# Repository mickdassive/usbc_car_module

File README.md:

# USB 3.1x1 Hub with USB-C and USB-A Ports

This project is a USB 3.1x1 hub designed with KiCad 8.0 and developed with PlatformIO. It features two USB-C ports (one downstream and one upstream) capable of delivering up to 100W power, along with four regular downstream USB-A ports.

## Features

- USB 3.1x1 hub with USB-C and USB-A ports
- Supports up to 100W power delivery per port
- Onboard UART transceiver for programming the main MCU (ESP-12F)
- Onboard CAN bus transceiver for automotive applications
- Utilizes USB5926C hub chip from Microchip
- USB PD PHYs (PTN110N) from NXP
- Includes a display and ADC for power monitoring:
  - Monitor individual power consumption of USB-C ports (upstream and downstream)
  - Monitor combined total power consumption of USB-A ports
  - Monitor total system power consumption

## Contributors

- [Tokyo Andreana](https://github.com/mickdassive)

## License

This project is licensed under the [GNU General Public License v3.0](LICENSE).

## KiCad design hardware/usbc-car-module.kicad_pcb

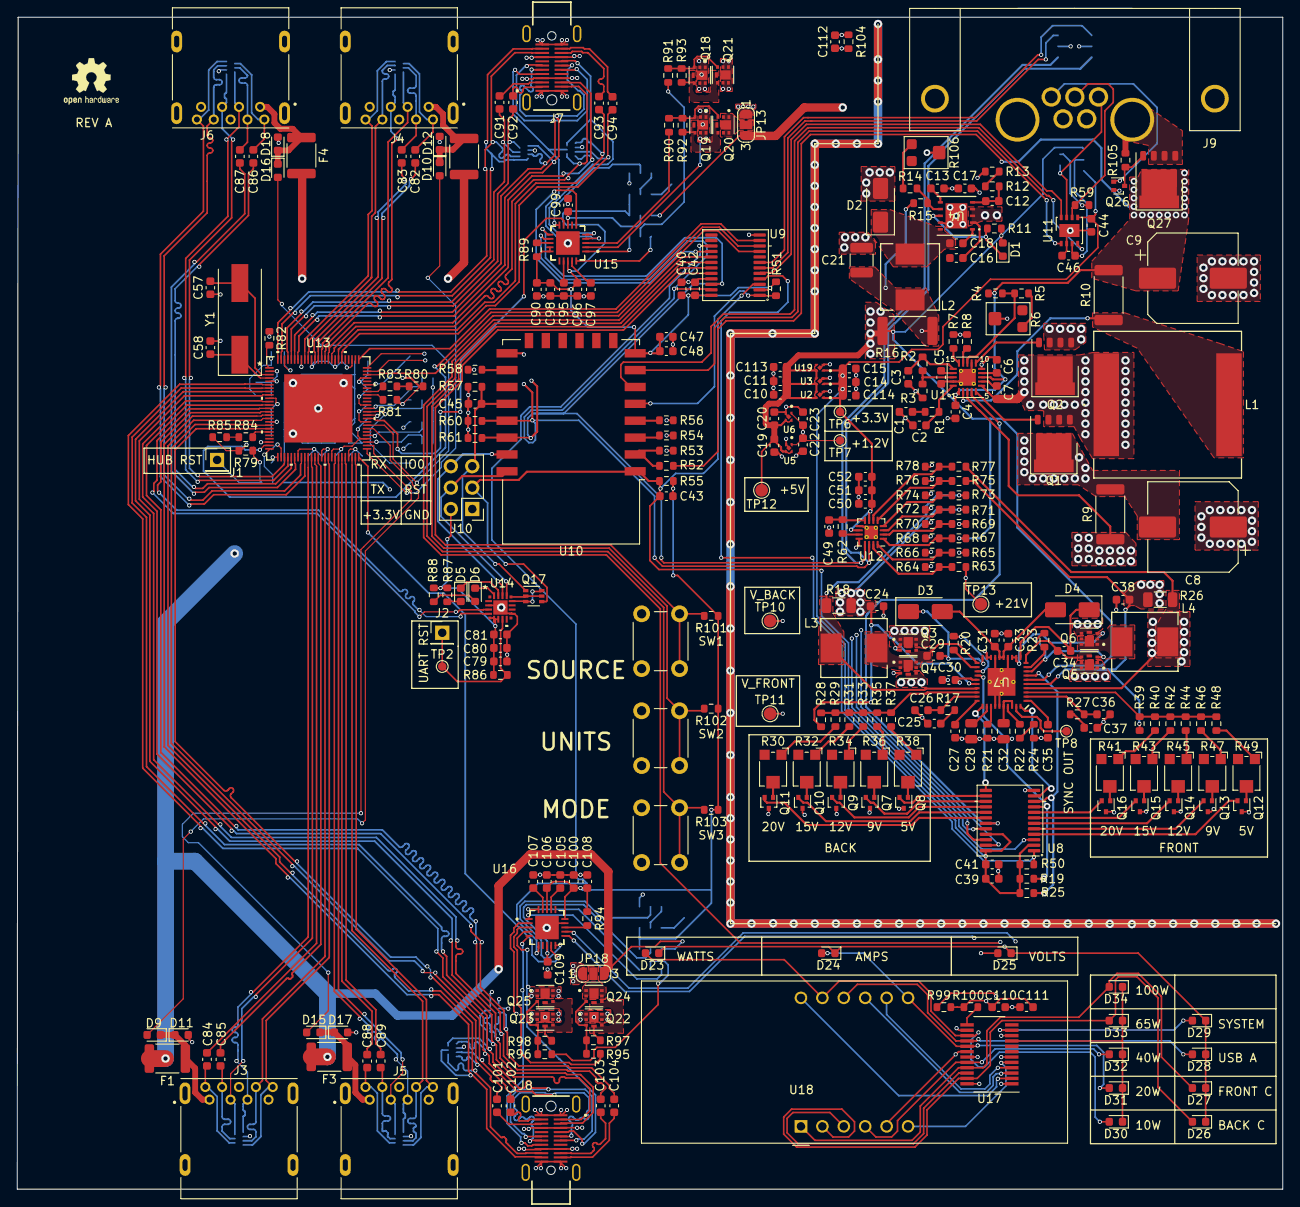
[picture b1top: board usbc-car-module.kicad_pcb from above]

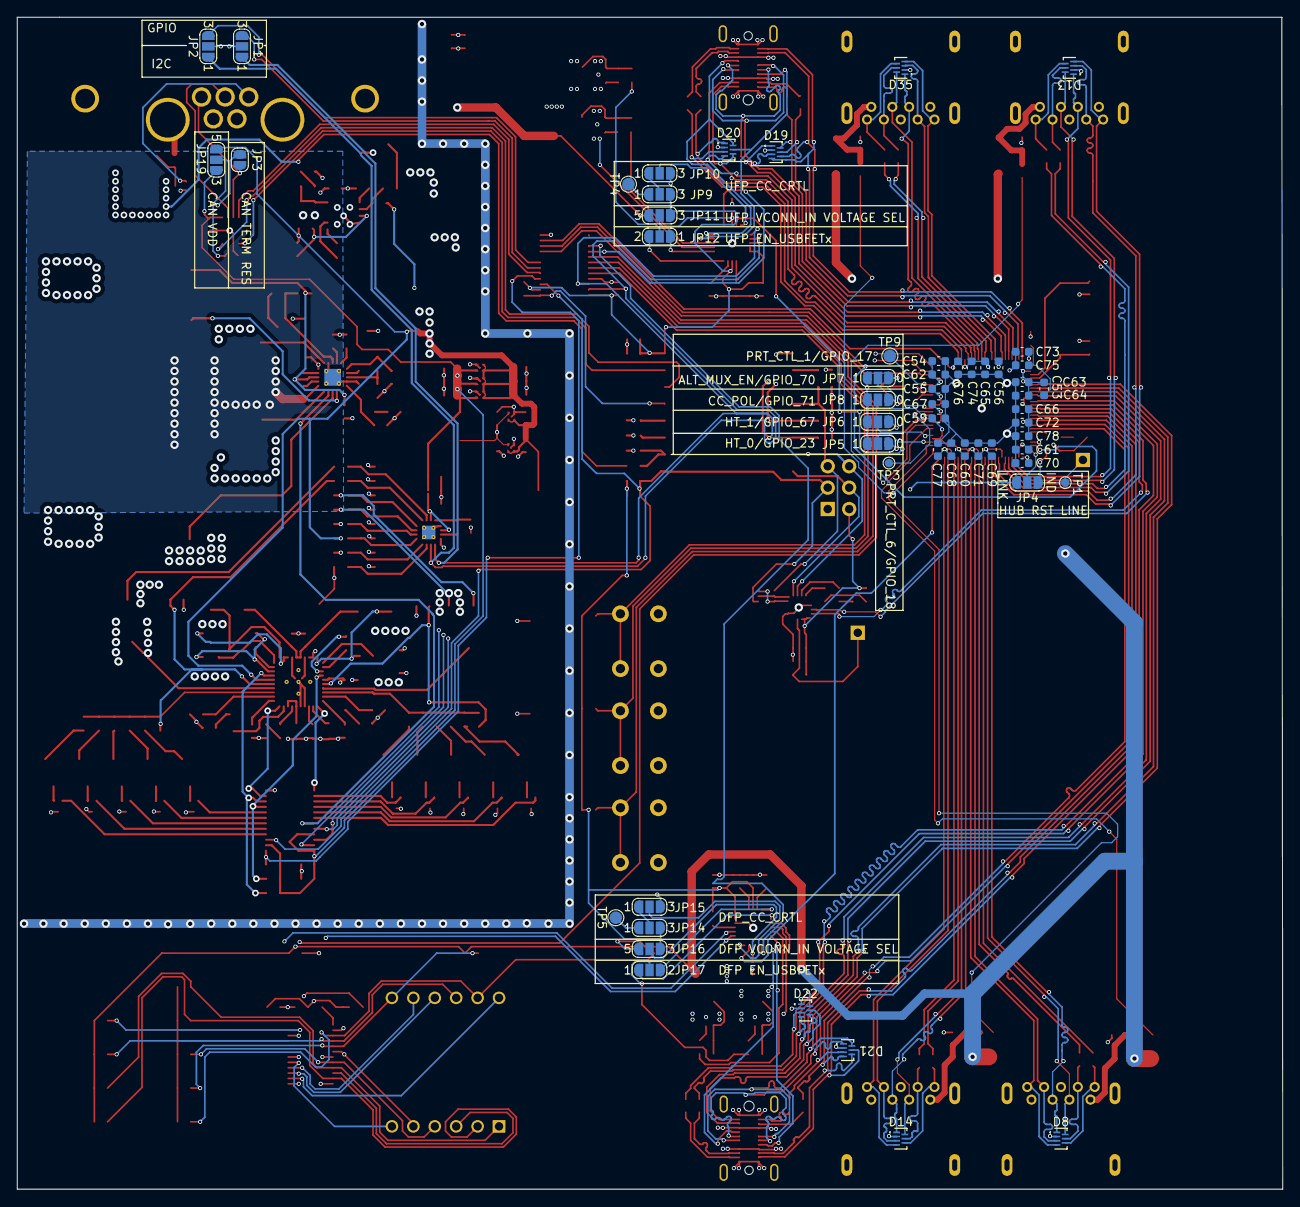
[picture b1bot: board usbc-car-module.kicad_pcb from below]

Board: 4 copper layers, 150.1 x 139.0 mm, 354 parts (54 on the bottom side), 290 nets.

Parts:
C1: 3uF3; C_0603_1608Metric
C2, C5, C7, C16, C18, C29, C34, C41, C42, C43, C44, C45, C46, C47, C50, C51, C55, C56, C59, C60, C61, C62, C63, C64, C65, C66, C67, C68, C69, C70, C71, C72, C73, C74, C76, C80, C81, C82, C83, C84, C85, C86, C87, C88, C89, C91, C92, C93, C94, C96, C98, C99, C101, C102, C103, C104, C106, C108, C109, C111, C112: 0.1uF; C_0603_1608Metric
C3, C4: 470pF; C_0603_1608Metric
C6, C17, C24, C25, C37, C38: 4.7uF; C_0603_1608Metric
C8: ouput cap EEEFK1V471SP 470uf; CP_Elec_10x10.5
C9: 120uF; CP_Elec_10x10.5
C10, C11, C13, C14, C15, C19, C20, C22, C23, C27, C35, C49, C113, C114: 1uF; C_0603_1608Metric
C12: 10pF; C_0603_1608Metric
C21: 15uF CGA6P3X7R1C156M250AB; C_1210_3225Metric
C26, C36, C57: 18pF; C_0603_1608Metric
C28, C32: 470nF; C_0805_2012Metric
C30: 50uF; C_0603_1608Metric
C31, C33, C95, C97, C105, C107: 2.2uF; C_0603_1608Metric
C39, C40, C48, C52, C53, C54, C75, C77, C78, C79, C90, C100, C110: 10uF; C_0603_1608Metric
C58: 18Pf; C_0603_1608Metric
D1, D5, D6: LED; D_0603_1608Metric
D2: SK510A-LTP; D_SMA
D3, D4: D_Shockley; D_SMA
D8, D13, D14, D19, D20, D21, D22, D35: PUSB3AB6Z_NEX
D9, D10, D15, D16: D; D_0603_1608Metric
D11, D12, D17, D18: uClamp0501H; D_0603_1608Metric
D23: W; D_0603_1608Metric
D24: A; D_0603_1608Metric
D25: V; D_0603_1608Metric
D26: BACK USBC POWER; D_0603_1608Metric
D27: FRONT USBC POWER; D_0603_1608Metric
D28: USBA POWER; D_0603_1608Metric
D29: TOTAL SYSTEM POWER; D_0603_1608Metric
D30: 10W; D_0603_1608Metric
D31: 20W; D_0603_1608Metric
D32: 40W; D_0603_1608Metric
D33: 65W; D_0603_1608Metric
D34: 100W; D_0603_1608Metric
F1, F3: 2A; Fuse_1812_4532Metric
F2, F4: 1A; Fuse_1812_4532Metric
J1, J2: PinHeader_1x01_P2.54mm_Vertical
J3, J4, J5, J6: 0483930003; MOLEX_0483930003
J7, J8: USB4200-03-A (VIRT FLAG MOUNTING); USB4200-03-A_REVA
J9: 684M7W2103L461
J10: PROG_PORT; PinHeader_2x03_P2.54mm_Vertical
JP1, JP2, JP4, JP5, JP6, JP7, JP8, JP9, JP10, JP11, JP12, JP13, JP14, JP15, JP16, JP17, JP18, JP19: SolderJumper-3_P1.3mm_Open_RoundedPad1.0x1.5mm_NumberLabels
JP3: SolderJumper-2_P1.3mm_Open_RoundedPad1.0x1.5mm
L1: IHLP6767GZER1R0M01; IND-6767GZ_VIS
L2: 1.2uH CR75NP-1R2MC; IND25X25CZ
L3, L4: IHLP2525CZER2R2M01; IND25X25CZ
Q1, Q2: NMOS; PQFN-8-EP_6x5mm_P1.27mm_Generic
Q3, Q4, Q5, Q6: PMPB11EN,115; TRANS_PMPB11EN_115
Q7, Q8, Q9, Q10, Q11, Q12, Q13, Q14, Q15, Q16, Q26: NMOS; SOT-416
Q17: BC847BS-7-F; SOT-363_SC-70-6
Q18, Q19, Q20, Q21, Q22, Q23, Q24, Q25: PMOS; TRANS_PMPB11EN_115
Q27: AON7421; PQFN-8-EP_6x5mm_P1.27mm_Generic
R1: 35K; R_0603_1608Metric
R2: 20K; R_0603_1608Metric
R3, R5, R7, R11, R12, R14, R22, R28, R33, R35, R39, R44, R46, R50, R51, R54, R55, R56, R57, R58, R63, R65, R67, R69, R71, R73, R75, R77, R79, R86, R89, R92, R93, R94, R97, R98, R99, R100, R101, R102, R103: 10K; R_0603_1608Metric
R4, R19, R25, R80, R83, R84, R85, R105: 100K; R_0603_1608Metric
R6, R106: 1K; Potentiometer_Bourns_TC33X_Vertical
R8, R21, R62: 0R; R_0603_1608Metric
R9, R10, R16: 1.5mR; R_2512_6332Metric
R13, R64, R66, R72, R74, R76, R78: 1K; R_0603_1608Metric
R15: 56K; R_0603_1608Metric
R17, R27: 5.9K; R_0603_1608Metric
R18, R26: 10mR; R_1206_3216Metric
R20: RHO1; R_0603_1608Metric
R23: RHO2; R_0603_1608Metric
R24, R53: 470R; R_0603_1608Metric
R29, R40: 30K; R_0603_1608Metric
R30, R32, R34, R36, R38, R41, R43, R45, R47, R49: 10K; Potentiometer_Bourns_TC33X_Vertical
R31, R42: 22K; R_0603_1608Metric
R37, R48, R68, R70: 5K; R_0603_1608Metric
R52, R60, R61: 10k; R_0603_1608Metric
R59: 120R; R_0603_1608Metric
R81: 10R; R_0603_1608Metric
R82: 12K 1%; R_0603_1608Metric
R87, R88, R104: 330R; R_0603_1608Metric
R90, R91, R95, R96: 15R; R_0603_1608Metric
SW1, SW2, SW3: SW_Push; SW_PUSH_6mm
TP1, TP3, TP6, TP7, TP8: TestPoint; TestPoint_Pad_D1.0mm
TP2: TestPoint_Pad_D1.0mm
TP4, TP5, TP9, TP10, TP11, TP12, TP13: TestPoint; TestPoint_Pad_D1.5mm
U1: LM51231-Q1; QFN-20-1EP_3.5x3.5mm_P0.5mm_EP2x2mm_ThermalVias
U2, U3, U19: NCP177BMX330TCG; VREG_NCP170AMX300TCG
U4: LMR14050-Q1; LMR14050
U5, U6: NCP177AMX120TCG; VREG_NCP170AMX300TCG
U7: LM5143
U8, U9: PI4IOE5V6416LEX; TSSOP-24_4.4x7.8mm_P0.65mm
U10: ESP-12F; ESP-12E
U11: MCP2558FD-xMF; DFN-8-1EP_3x3mm_P0.65mm_EP1.55x2.4mm
U12: WQFN-16-1EP_3x3mm_P0.5mm_EP1.6x1.6mm_ThermalVias
U13: VQFN100_KD_MCH
U14: CP2102N-QFN20; QFN20_SIL
U15, U16: PTN5100BSMP
U17: AS1115-BSST; QSOP-24_3.9x8.7mm_P0.635mm
U18: LTC-5723HR; CA56-12CGKWA
Y1: 25MHz; Crystal_SMD_HC49-SD

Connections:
5V_ADC: R67.2, R68.1, U12.1 (AIN2/GPIO2)
5V_CSN: C21.1, L2.2, R15.2, R16.1, R69.1
5V_CSN_ADC: R69.2, R70.1, U12.2 (AIN3/GPIO3)
21V_ADC: R63.2, R64.1, U12.15 (AIN0/GPIO0)
21V_COMP: C2.1, R1.1, U1.20 (COMP)
21V_CSN: C8.2, Q1.5 (D), R9.1, R65.1
21V_CSN_ADC: R65.2, R66.1, U12.16 (AIN1/GPIO1)
21V_PGOOD: U1.4 (PGOOD), U8.19 (P1_6)
+1V2: C22.1, C23.1, C65.2, C66.1, C67.2, C68.1, C69.2, C70.1, C71.2, C72.1, C73.2, C74.1, C75.2, C76.1, C77.2, C78.1, TP7.1, U5.1 (OUT), U6.1 (OUT), U13.10 (VDD12), U13.17 (VDD12), U13.26 (VDD12), U13.32 (VDD12), U13.39 (VDD12), U13.47 (VDD12), U13.59 (VDD12), U13.78 (VDD12), U13.83 (VDD12), U13.90 (VDD12), U13.98 (VDD12)
+3V3: C14.1, C15.1, C39.1, C40.1, C41.1, C42.1, C43.1, C44.2, C45.1, C47.1, C48.1, C50.1, C51.1, C52.1, C53.1, C54.2, C55.1, C56.2, C59.1, C60.2, C61.1, C62.2, C63.1, C64.2, C79.1, C80.1, C81.1, C90.1, C96.1, C98.1, C100.1, C106.1, C108.1, C110.1, C111.1, C114.1, J10.2, JP5.1 (A), JP6.1 (A), JP7.1 (A), JP8.1 (A), JP9.3 (B), JP11.3 (B), JP14.3 (B), JP16.3 (B), JP19.1 (A), R19.1, R25.2, R50.1, R51.1, R54.1, R55.1, R57.1, R60.1, R61.1, R79.2, R85.2, R86.1, R87.2, R88.2, R89.2, R94.2, R99.1, R100.1, R101.1, R102.1, R103.1, TP6.1, U2.1 (OUT), U3.1 (OUT), U8.2 (VDD_I2C), U8.21 (ADDR), U8.24 (VDD), U9.2 (VDD_I2C), U9.24 (VDD), U10.8 (VCC), U11.5 (VIO), U12.7 (AVDD), U12.10 (DVDD), U13.2 (VDD33), U13.5 (VDD33), U13.27 (VDD33), U13.42 (VDD33), U13.54 (VDD33), U13.64 (VDD33), U13.72 (VDD33), U13.93 (VDD33), U14.6 (VDD), U14.7 (VREGIN), U14.8 (VBUS), U15.14 (SLV_ADDR), U15.15 (VDD), U15.18 (VIO), U16.15 (VDD), U16.18 (VIO), U17.19 (VDD), U19.1 (OUT)
+5V: C10.1, C11.1, C19.1, C20.1, C113.1, D1.2 (A), F1.2, F2.2, F3.2, F4.2, JP11.1 (A), JP13.3 (B), JP16.1 (A), JP18.3 (B), JP19.3 (B), R11.1, R16.2, R67.1, TP12.1, U2.3 (EN), U2.4 (IN), U3.3 (EN), U3.4 (IN), U5.3 (EN), U5.4 (IN), U6.3 (EN), U6.4 (IN), U7.6 (VCCX), U19.3 (EN), U19.4 (IN)
+21V: C16.1, C17.1, C30.2, Q3.1 (D), Q3.2 (D), Q3.5 (D), Q3.6 (D), Q3.7 (D), Q5.1 (D), Q5.2 (D), Q5.5 (D), Q5.6 (D), Q5.7 (D), R9.2, R63.1, TP13.1, U1.3 (VOUT/SENSE), U4.2 (VIN), U4.3 (VIN), U4.4 (EN), U7.25 (VIN)
/5V USB-A AND MCU POWER/5V_BOOT: C18.1, U4.1 (BOOT)
/5V USB-A AND MCU POWER/5V_FB: R14.2, R15.1, U4.7 (FB)
/5V USB-A AND MCU POWER/5V_RT: R12.2, R13.1
/5V USB-A AND MCU POWER/5V_SS: C13.1, U4.6 (SS)
/5V USB-A AND MCU POWER/5V_SW: C18.2, D2.1 (K), L2.1, U4.10 (SW)
/12-21V INPUT BOOST CONVERTER/21V_COMP_1: C1.1, R1.2
/12-21V INPUT BOOST CONVERTER/21V_VCC: C6.1, U1.9 (VCC)
/12-21V INPUT BOOST CONVERTER/CSN: L1.2, R10.1, U1.2 (CSN)
/12-21V INPUT BOOST CONVERTER/HB: C7.1, U1.7 (HB)
/12-21V INPUT BOOST CONVERTER/HI_SW: Q1.4 (G), U1.5 (HO)
/12-21V INPUT BOOST CONVERTER/LO_SW: Q2.4 (G), U1.11 (LO)
/12-21V INPUT BOOST CONVERTER/RT: R7.2, U1.15 (RT)
/12-21V INPUT BOOST CONVERTER/SS: C5.2, U1.17 (SS)
/12-21V INPUT BOOST CONVERTER/SW: C7.2, L1.1, Q1.1 (S), Q1.2 (S), Q1.3 (S), Q2.5 (D), U1.6 (SW)
/12-21V INPUT BOOST CONVERTER/TRK: R2.2, R3.1, U1.18 (TRK)
/12-21V INPUT BOOST CONVERTER/UVLO/EN: R4.2, R5.1, U1.13 (UVLO/EN)
/12-21V INPUT BOOST CONVERTER/VREF: C3.1, R2.1, U1.16 (VREF/RANGE)
/BACK_UFP_USB_C_PORT/UFP_TXA_N: C91.1, J7.A3 (TX1-)
/BACK_UFP_USB_C_PORT/UFP_TXA_P: C92.2, J7.A2 (TX1+)
/BACK_UFP_USB_C_PORT/UFP_TXB_N: C93.1, J7.B3 (TX2-)
/BACK_UFP_USB_C_PORT/UFP_TXB_P: C94.2, J7.B2 (TX2+)
/FRONT_DFP_USB_C_PORT/DFP_RXA_N: C103.1, J8.A10 (RX2-)
/FRONT_DFP_USB_C_PORT/DFP_RXA_P: C104.2, J8.A11 (RX2+)
/FRONT_DFP_USB_C_PORT/DFP_RXB_N: C101.1, J8.B10 (RX1-)
/FRONT_DFP_USB_C_PORT/DFP_RXB_P: C102.2, J8.B11 (RX1+)
/USBA_PORTS/P2_2_N: D8.7 (CH6), J3.2 (D-), U13.36 (USB2DN_DM3/PRT_DIS_M3)
/USBA_PORTS/P2_2_P: D8.1 (CH1), J3.3 (D+), U13.35 (USB2DN_DP3/PRT_DIS_P3)
/USBA_PORTS/P2_RX_N: D8.4 (CH3), J3.5 (STDA_SSRX-), U13.41 (USB3DN_RXDM3)
/USBA_PORTS/P2_RX_P: D8.3 (CH2), J3.6 (STDA_SSRX+), U13.40 (USB3DN_RXDP3)
/USBA_PORTS/P2_TXP_N: C85.1, D8.6 (CH5), J3.8 (STDA_SSTX-)
/USBA_PORTS/P2_TXP_P: C84.2, D8.5 (CH4), J3.9 (STDA_SSTX+)
/USBA_PORTS/P2_TX_N: C85.2, U13.38 (USB3DN_TXDM3)
/USBA_PORTS/P2_TX_P: C84.1, U13.37 (USB3DN_TXDP3)
/USBA_PORTS/P3_2_N: D14.7 (CH6), J5.2 (D-), U13.44 (USB2DN_DM4/PRT_DIS_M4)
/USBA_PORTS/P3_2_P: D14.1 (CH1), J5.3 (D+), U13.43 (USB2DN_DP4/PRT_DIS_P4)
/USBA_PORTS/P3_RX_N: D14.4 (CH3), J5.5 (STDA_SSRX-), U13.49 (USB3DN_RXDM4)
/USBA_PORTS/P3_RX_P: D14.3 (CH2), J5.6 (STDA_SSRX+), U13.48 (USB3DN_RXDP4)
/USBA_PORTS/P3_TXP_N: C89.1, D14.6 (CH5), J5.8 (STDA_SSTX-)
/USBA_PORTS/P3_TXP_P: C88.2, D14.5 (CH4), J5.9 (STDA_SSTX+)
/USBA_PORTS/P3_TX_N: C89.2, U13.46 (USB3DN_TXDM4)
/USBA_PORTS/P3_TX_P: C88.1, U13.45 (USB3DN_TXDP4)
/USBA_PORTS/P4_2_N: D35.7 (CH6), J4.2 (D-), U13.87 (USB2DN_DM5/PRT_DIS_M5)
/USBA_PORTS/P4_2_P: D35.1 (CH1), J4.3 (D+), U13.86 (USB2DN_D5/PRT_DIS_P5)
/USBA_PORTS/P4_RX_N: D35.4 (CH3), J4.5 (STDA_SSRX-), U13.92 (USB3DN_RXDM5)
/USBA_PORTS/P4_RX_P: D35.3 (CH2), J4.6 (STDA_SSRX+), U13.91 (USB3DN_RXDP5)
/USBA_PORTS/P4_TXP_N: C83.1, D35.6 (CH5), J4.8 (STDA_SSTX-)
/USBA_PORTS/P4_TXP_P: C82.2, D35.5 (CH4), J4.9 (STDA_SSTX+)
/USBA_PORTS/P4_TX_N: C83.2, U13.89 (USB3DN_TXDM5)
/USBA_PORTS/P4_TX_P: C82.1, U13.88 (USB3DN_TXDP5)
/USBA_PORTS/P5_2_N: D13.7 (CH6), J6.2 (D-), U13.29 (USB2DN_DM2/PRT_DIS_M2)
/USBA_PORTS/P5_2_P: D13.1 (CH1), J6.3 (D+), U13.28 (USB2DN_DP2/PRT_DIS_P2)
/USBA_PORTS/P5_RX_N: D13.4 (CH3), J6.5 (STDA_SSRX-), U13.34 (USB3DN_RXDM2)
/USBA_PORTS/P5_RX_P: D13.3 (CH2), J6.6 (STDA_SSRX+), U13.33 (USB3DN_RXDP2)
/USBA_PORTS/P5_TXP_N: C87.1, D13.6 (CH5), J6.8 (STDA_SSTX-)
/USBA_PORTS/P5_TXP_P: C86.2, D13.5 (CH4), J6.9 (STDA_SSTX+)
/USBA_PORTS/P5_TX_N: C87.2, U13.31 (USB3DN_TXDM2)
/USBA_PORTS/P5_TX_P: C86.1, U13.30 (USB3DN_TXDP2)
/USB_UART/USB_UART_N: U13.14 (USB2DN_DM6/PRT_DIS_M6), U14.5 (D-)
/USB_UART/USB_UART_P: U13.13 (USB2DN_DP6/PRT_DIS_P6), U14.4 (D+)
ADC_ALERT: U8.20 (P1_7), U12.12 (ALERT)
B_SUB-C_BUCK_P-GOOD: R19.2, U7.24 (PG1), U8.9 (P0_5)
B_USB-C_BUCK_5V_SEL: Q8.2 (G), U8.14 (P1_1)
B_USB-C_BUCK_9V_SEL: Q7.2 (G), U8.15 (P1_2)
B_USB-C_BUCK_12V_SEL: Q9.2 (G), U8.16 (P1_3)
B_USB-C_BUCK_15V_SEL: Q10.2 (G), U8.17 (P1_4)
B_USB-C_BUCK_20V_SEL: Q11.2 (G), U8.18 (P1_5)
B_USB-C_BUCK_EN: U7.31 (EN1), U8.13 (P1_0)
B_USB-C_BUCK_FB: R28.2, R29.1, R31.1, R33.1, R35.1, R37.1, U7.28 (FB1)
B_USB-C_BUCK_OUT: C24.1, JP13.1 (A), Q21.1 (D), Q21.2 (D), Q21.5 (D), Q21.6 (D), Q21.7 (D), R18.1, R28.1, R71.1, TP10.1, U7.26 (VOUT1)
B_USB-C_BUCK_OUT_ADC: R71.2, R72.1, U12.3 (AIN4/GPIO4)
B_USB-C_CSN: L3.1, R18.2, R73.1, U7.27 (CS1)
B_USB-C_CSN_ADC: R73.2, R74.1, U12.4 (AIN5/GPIO5)
CAN_H: J9.3, JP3.2 (B), U11.7 (CANH)
CAN_L: J9.4, R59.2, U11.6 (CANL)
CAN_RX: U10.6 (GPIO12), U11.4 (RXD)
CAN_SILENT: U9.5 (P0_1), U11.8 (S)
CAN_TX: U10.7 (GPIO13), U11.1 (TXD)
CAR_12V_IN: C4.1, C9.1, Q27.5 (D), R4.1, R10.2, R52.1, U1.1 (CSP), U1.8 (BIAS)
DFP_2_N: D21.7 (CH6), J8.A7 (D-), J8.B7 (D-), U13.7 (USB2DN_DM1/PRT_DIS_M1)
DFP_2_P: D21.1 (CH1), J8.A6 (D+), J8.B6 (D+), U13.6 (USB2DN_DP1/PRT_DIS_P1)
DFP_3_RXA_N: C103.2, D22.4 (CH3), U13.12 (USB3DN_RXDM1A)
DFP_3_RXA_P: C104.1, D22.3 (CH2), U13.11 (USB3DN_RXDP1A)
DFP_3_RXB_N: C101.2, D21.4 (CH3), U13.19 (USB3DN_RXDM1B)
DFP_3_RXB_P: C102.1, D21.3 (CH2), U13.18 (USB3DN_RXDP1B)
DFP_3_TXA_N: D22.5 (CH4), J8.A3 (TX1-), U13.9 (USB3DN_TXDM1A)
DFP_3_TXA_P: D22.6 (CH5), J8.A2 (TX1+), U13.8 (USB3DN_TXDP1A)
DFP_3_TXB_N: D21.5 (CH4), J8.B3 (TX2-), U13.16 (USB3DN_TXDM1B)
DFP_3_TXB_P: D21.6 (CH5), J8.B2 (TX2+), U13.15 (USB3DN_TXDP1B)
DFP_CC1: D22.7 (CH6), J8.A5 (CC1), U16.4 (CC2)
DFP_CC2: D22.1 (CH1), J8.B5 (CC2), U16.5 (CC1)
DFP_CC_CTRL: JP15.2 (C), U16.10 (CC_CRTL1)
DFP_CC_ORIENT: U13.50 (AB1/ATTACHMUX1B/GPIO65), U16.9 (CC_ORIENT)
DFP_C_ATTACH_1: U9.9 (P0_5), U13.73 (C_ATTACH1/ATTACHMUX1A/GPIO1)
DFP_DBGACC: U9.15 (P1_2), U16.6 (DBGACC_FOUND)
DFP_PD_INT: R94.1, U16.13 (INT_N)
DFP_VBUS: J8.A4 (VBUS), J8.A9 (VBUS), J8.B4 (VBUS), J8.B9 (VBUS), Q22.1 (D), Q22.2 (D), Q22.5 (D), Q22.6 (D), Q22.7 (D), Q23.1 (D), Q23.2 (D), Q23.5 (D), Q23.6 (D), Q23.7 (D), U16.2 (VBUS)
DISP_DIG_0: U17.2 (DIG0), U18.12 (CC1)
DISP_DIG_1: U17.3 (DIG1), U18.9 (CC2)
DISP_DIG_2: U17.4 (DIG2), U18.8 (CC3)
DISP_DIG_3: U17.5 (DIG3), U18.6 (CC4)
DISP_DIG_6: D30.1 (K), D31.1 (K), D32.1 (K), D33.1 (K), D34.1 (K), U17.9 (DIG6)
DISP_DIG_7: D23.1 (K), D24.1 (K), D25.1 (K), D26.1 (K), D27.1 (K), D28.1 (K), D29.1 (K), U17.10 (DIG7)
DISP_IRQ: R99.2, U9.17 (P1_4), U17.24 (IRQ)
DISP_SEG_A: D23.2 (A), D30.2 (A), U17.15 (SEGA), U18.11 (a)
DISP_SEG_B: D24.2 (A), D31.2 (A), U17.17 (SEGB), U18.7 (b)
DISP_SEG_C: D25.2 (A), D32.2 (A), U17.20 (SEGC), U18.4 (c)
DISP_SEG_D: D26.2 (A), D33.2 (A), U17.23 (SEGD), U18.2 (d)
DISP_SEG_DP: U17.22 (SEGDP), U18.3 (DPX)
DISP_SEG_E: D27.2 (A), D34.2 (A), U17.21 (SEGE), U18.1 (e)
DISP_SEG_F: D28.2 (A), U17.16 (SEGF), U18.10 (f)
DISP_SEG_G: D29.2 (A), U17.11 (KEYA), U17.18 (SEGG), U18.5 (g)
DSUB_P_6: J9.6, JP2.2 (C)
DSUB_P_7: J9.7, JP1.2 (C)
ESP_EN: R54.2, U10.3 (EN)
ESP_IO0: C45.2, J10.5, Q17.1 (C1), R57.2, U10.18 (GPIO0)
ESP_RX: J10.6, U10.21 (GPIO3/RXD), U14.18 (TXD)
ESP_TX: J10.4, U10.22 (GPIO1/TXD), U14.17 (RXD)
F_SUB-C_BUCK_P-GOOD: R25.1, U7.7 (PG2), U8.10 (P0_6)
F_USB-C_BUCK_5V_SEL: Q12.2 (G), U8.4 (P0_0)
F_USB-C_BUCK_9V_SEL: Q13.2 (G), U8.5 (P0_1)
F_USB-C_BUCK_12V_SEL: Q14.2 (G), U8.6 (P0_2)
F_USB-C_BUCK_15V_SEL: Q15.2 (G), U8.7 (P0_3)
F_USB-C_BUCK_20V_SEL: Q16.2 (G), U8.8 (P0_4)
F_USB-C_BUCK_EN: U7.40 (EN2), U8.11 (P0_7)
F_USB-C_BUCK_FB: R39.2, R40.1, R42.1, R44.1, R46.1, R48.1, U7.3 (FB2)
F_USB-C_BUCK_OUT: C38.1, JP18.1 (A), Q25.1 (D), Q25.2 (D), Q25.5 (D), Q25.6 (D), Q25.7 (D), R26.2, R39.1, R75.1, TP11.1, U7.5 (VOUT2)
F_USB-C_BUCK_OUT_ADC: R75.2, R76.1, U12.5 (AIN6/GPIO6)
F_USB-C_CSN: L4.2, R26.1, R77.1, U7.4 (CS2)
F_USB-C_CSN_ADC: R77.2, R78.1, U12.6 (AIN7/GPIO7)
GND: C1.2, C2.2, C3.2, C4.2, C5.1, C6.2, C8.1, C9.2, C10.2, C11.2, C13.2, C14.2, C15.2, C16.2, C17.2, C19.2, C20.2, C21.2, C22.2, C23.2, C24.2, C25.1, C26.1, C27.1, C28.1, C30.1, C31.2, C32.1, C33.2, C35.1, C36.2, C37.2, C38.2, C39.2, C40.2, C41.2, C42.2, C44.1, C46.2, C47.2, C48.2, C49.2, C50.2, C51.2, C52.2, C53.2, C54.1, C55.2, C56.1, C57.1, C58.1, C59.2, C60.1, C61.2, C62.1, C63.2, C64.1, C65.1, C66.2, C67.1, C68.2, C69.1, C70.2, C71.1, C72.2, C73.1, C74.2, C75.1, C76.2, C77.1, C78.2, C79.2, C80.2, C81.2, C90.2, C95.2, C96.2, C97.2, C98.2, C99.2, C100.2, C105.2, C106.2, C107.2, C108.2, C109.2, C110.2, C111.2, C112.1, C113.2, C114.2, D2.2 (A), D8.2 (GND), D11.2 (A), D12.2 (A), D13.2 (GND), D14.2 (GND), D17.2 (A), D18.2 (A), D19.2 (GND), D20.2 (GND), D21.2 (GND), D22.2 (GND), D35.2 (GND), J3.4 (GND), J3.7 (GND_DRAIN), J4.4 (GND), J4.7 (GND_DRAIN), J5.4 (GND), J5.7 (GND_DRAIN), J6.4 (GND), J6.7 (GND_DRAIN), J7.A1 (GND), J7.A12 (GND), J7.B1 (GND), J7.B12 (GND), J8.A1 (GND), J8.A12 (GND), J8.B1 (GND), J8.B12 (GND), J9.2, J10.1, JP5.3 (B), JP6.3 (B), JP7.3 (B), JP8.3 (B), JP10.3 (B), JP15.3 (B), Q2.1 (S), Q2.2 (S), Q2.3 (S), Q4.4 (S), Q4.8 (S), Q6.4 (S), Q6.8 (S), Q7.3 (S), Q8.3 (S), Q9.3 (S), Q10.3 (S), Q11.3 (S), Q12.3 (S), Q13.3 (S), Q14.3 (S), Q15.3 (S), Q16.3 (S), Q26.2 (S), R3.2, R6.2, R7.1, R8.2, R13.2, R21.2, R24.2, R53.2, R56.2, R58.2, R64.2, R66.2, R68.2, R70.2, R72.2, R74.2, R76.2, R78.2, R80.2, R81.2, R82.1, R104.1, R106.2, SW1.2, SW2.2, SW3.2, U1.10 (PGND), U1.12 (MODE), U1.19 (AGND), U1.21 (EP), U2.2 (GND), U2.5 (EP), U3.2 (GND), U3.5 (EP), U4.9 (GND), U4.11 (EP), U5.2 (GND), U5.5 (EP), U6.2 (GND), U6.5 (EP), U7.14 (PGND2), U7.17 (PGND1), U7.34 (MODE), U7.35 (AGND), U7.41 (EP), U8.12 (VSS), U9.12 (VSS), U9.21 (ADDR), U10.15 (GND), U11.2 (VSS), U11.9 (VSS), U12.9 (GND), U12.17 (EP), U13.23 (TESTEN), U13.101 (VSS/GND), U14.3 (GND), U14.12 (GND), U14.21 (GND), U15.21 (GND), U16.14 (SLV_ADDR), U16.21 (GND), U17.6 (GND), U19.2 (GND), U19.5 (EP)
GNDS: C112.2, J3.S, J4.S, J5.S, J6.S, J7.S (SHIELD), J8.S (SHIELD), J9.S, R104.2
HUB_VBUS_DET: U9.10 (P0_6), U13.24 (VBUS_DET)
I2C_SCL: JP1.1 (A), R61.2, U8.22 (SCL), U9.22 (SCL), U10.20 (GPIO5), U12.13 (SCL), U13.75 (SMBCLK/GPIO8/SCL), U15.11 (SPI_CLK_I2C_SCL), U16.11 (SPI_CLK_I2C_SCL), U17.14 (SCL)
I2C_SDA: JP2.1 (A), R60.2, U8.23 (SDA), U9.23 (SDA), U10.19 (GPIO4), U12.14 (SDA), U13.74 (SMBDATA/GPIO6/SDA), U15.12 (SPI_MOSI_I2C_SDA), U16.12 (SPI_MOSI_I2C_SDA), U17.1 (SDA)
IOX0_INT: R51.2, U9.1 (INT), U10.5 (GPIO14)
IOX1_INT: R50.2, U8.1 (INT), U9.4 (P0_0)
IOX_0_P_0_0: JP2.3 (B), U9.7 (P0_3)
IOX_0_P_0_1: JP1.3 (B), U9.6 (P0_2)
MAIN BOOST CLOCK IN: R8.1, U1.14 (SYNC/DITHER/EN)
MODE_BTN: R103.2, SW3.1, U9.18 (P1_5)
unnamed: C25.2, R17.1
unnamed: C37.1, R27.2
unnamed: D1.1 (K), R11.2, U4.8 (PGOOD)
unnamed: C31.1, C33.1, D3.2 (A), D4.2 (A), U7.15 (VCC), U7.16 (VCC)
unnamed: C29.2, D3.1 (K), U7.20 (HB1)
unnamed: C34.1, D4.1 (K), U7.11 (HB2)
unnamed: D5.2 (A), R87.1
unnamed: D5.1 (K), U14.19 (~RXT/GPIO.3)
unnamed: D6.2 (A), R88.1
unnamed: D6.1 (K), U14.20 (~TXT/GPIO.2)
unnamed: D9.2 (A), U13.57 (PRT_CTL3/GANG_PWR/GPIO20)
unnamed: D10.2 (A), U13.51 (PRT_CTL5/GPIO22)
unnamed: D10.1 (K), D12.1 (K), F2.1, J4.1 (VBUS)
unnamed: D9.1 (K), D11.1 (K), F1.1, J3.1 (VBUS)
unnamed: D15.2 (A), U13.52 (PRT_CTL4/GPIO21)
unnamed: D15.1 (K), D17.1 (K), F3.1, J5.1 (VBUS)
unnamed: D16.2 (A), U13.58 (PRT_CTL2/GPIO19)
unnamed: D16.1 (K), D18.1 (K), F4.1, J6.1 (VBUS)
unnamed: J1.1, JP4.1 (A), R79.1, TP1.1
unnamed: J9.1, Q27.1 (S), Q27.2 (S), Q27.3 (S), R105.1
unnamed: JP3.1 (A), R59.1
unnamed: JP4.2 (C), U13.25 (RESET_N)
unnamed: JP5.2 (C), U13.53 (HOST_TYPE0/GPIO23)
unnamed: JP6.2 (C), U13.55 (HOST_TYPE1/GPIO67)
unnamed: JP7.2 (C), U13.63 (ALT_MUX_EN/GPIO70)
unnamed: JP8.2 (C), U13.61 (CC_POL/GPIO71)
unnamed: JP9.1 (A), TP4.1
unnamed: JP9.2 (C), JP10.1 (A)
unnamed: C99.1, JP11.2 (C), U15.8 (VCONN_IN)
unnamed: JP12.1 (A), U15.20 (EN_USBFET2)
unnamed: JP12.3 (B), U15.1 (EN_USBFET1)
unnamed: JP12.2 (C), R91.1
unnamed: JP13.2 (C), Q20.1 (D), Q20.2 (D), Q20.5 (D), Q20.6 (D), Q20.7 (D)
unnamed: JP14.1 (A), TP5.1
unnamed: JP14.2 (C), JP15.1 (A)
unnamed: C109.1, JP16.2 (C), U16.8 (VCONN_IN)
unnamed: JP17.1 (A), U16.1 (EN_USBFET1)
unnamed: JP17.3 (B), U16.20 (EN_USBFET2)
unnamed: JP17.2 (C), R96.1
unnamed: JP18.2 (C), Q24.1 (D), Q24.2 (D), Q24.5 (D), Q24.6 (D), Q24.7 (D)
unnamed: C46.1, JP19.2 (C), U11.3 (VDD)
unnamed: Q3.3 (G), R20.1, U7.23 (HOL1)
unnamed: Q4.3 (G), U7.18 (LO1), U7.19 (LOL1)
unnamed: Q5.3 (G), R23.2, U7.8 (HOL2)
unnamed: Q6.3 (G), U7.12 (LOL2), U7.13 (LO2)
unnamed: Q7.1 (D), R36.2
unnamed: Q8.1 (D), R38.2
unnamed: Q9.1 (D), R34.2
unnamed: Q10.1 (D), R32.2
unnamed: Q11.1 (D), R30.2
unnamed: Q12.1 (D), R49.2
unnamed: Q13.1 (D), R47.2
unnamed: Q14.1 (D), R45.2
unnamed: Q15.1 (D), R43.2
unnamed: Q16.1 (D), R41.2
unnamed: Q17.2 (B1), Q17.5 (E2), U14.16 (~RTS)
unnamed: Q17.3 (B2), Q17.6 (E1), U14.15 (~CTS)
unnamed: Q18.3 (G), Q21.3 (G), R91.2, R93.2
unnamed: Q18.4 (S), Q18.8 (S), Q21.4 (S), Q21.8 (S), R93.1
unnamed: Q19.3 (G), Q20.3 (G), R90.2, R92.2
unnamed: Q19.4 (S), Q19.8 (S), Q20.4 (S), Q20.8 (S), R92.1
unnamed: Q22.3 (G), Q24.3 (G), R95.2, R97.2
unnamed: Q22.4 (S), Q22.8 (S), Q24.4 (S), Q24.8 (S), R97.1
unnamed: Q23.3 (G), Q25.3 (G), R96.2, R98.2
unnamed: Q23.4 (S), Q23.8 (S), Q25.4 (S), Q25.8 (S), R98.1
unnamed: Q26.3 (D), Q27.4 (G), R105.2
unnamed: J9.5, Q26.1 (G)
unnamed: R5.2, R6.1
unnamed: R22.2, R24.1
unnamed: R29.2, R30.1
unnamed: R31.2, R32.1
unnamed: R33.2, R34.1
unnamed: R35.2, R36.1
unnamed: R37.2, R38.1
unnamed: R40.2, R41.1
unnamed: R42.2, R43.1
unnamed: R44.2, R45.1
unnamed: R46.2, R47.1
unnamed: R48.2, R49.1
unnamed: R80.1, R83.2
unnamed: R84.2, R85.1
unnamed: R14.1, R106.1
unnamed: C26.2, R17.2, U7.29 (COMP1)
unnamed: C36.1, R27.1, U7.2 (COMP2)
unnamed: C32.2, U7.36 (VDDA), U7.38 (DITH)
unnamed: R20.2, U7.22 (HO1)
unnamed: R23.1, U7.9 (HO2)
unnamed: C28.2, U7.32 (RES)
unnamed: R22.1, U7.37 (RT)
unnamed: C27.2, U7.30 (SS1)
unnamed: C35.2, U7.1 (SS2)
unnamed: C29.1, L3.2, Q3.4 (S), Q3.8 (S), Q4.1 (D), Q4.2 (D), Q4.5 (D), Q4.6 (D), Q4.7 (D), U7.21 (SW1)
unnamed: C34.2, L4.1, Q5.4 (S), Q5.8 (S), Q6.1 (D), Q6.2 (D), Q6.5 (D), Q6.6 (D), Q6.7 (D), U7.10 (SW2)
unnamed: TP8.1, U7.39 (SYNCOUT)
unnamed: R52.2, R53.1, U10.2 (ADC)
unnamed: R58.1, U10.16 (GPIO15)
unnamed: R56.1, U10.4 (GPIO16)
unnamed: R62.2, U12.11 (ADDR)
unnamed: C49.1, R62.1, U12.8 (DECAP)
unnamed: R84.1, U13.20 (CFG_STRAP/GPIO12)
unnamed: R82.2, U13.1 (RBAIS)
unnamed: C57.2, U13.3 (XTALI/CLKIN), Y1.2
unnamed: C58.2, U13.4 (XTALO), Y1.1
unnamed: R83.1, U13.68 (SPI_CE_N/GPIO7/CFG_NON_REM)
unnamed: R81.1, U13.67 (SPI_DI/GPIO9/CFG_BC_EN)
unnamed: TP9.1, U13.70 (PRT_CTL1/GPIO17)
unnamed: TP3.1, U13.62 (PRT_CTL6/GPIO18)
unnamed: C97.1, U15.19 (BYPASS)
unnamed: R90.1, U15.3 (EN_USBSRC)
unnamed: C95.1, U15.17 (V_MCUPWR)
unnamed: C107.1, U16.19 (BYPASS)
unnamed: R95.1, U16.3 (EN_USBSRC)
unnamed: C105.1, U16.17 (V_MCUPWR)
unnamed: R100.2, U17.13 (ISET)
RST: C43.2, J10.3, JP4.3 (B), Q17.4 (C2), R55.2, U8.3 (RESET), U9.3 (RESET), U10.1 (~RST)
SRC_BTN: R101.2, SW1.1, U9.20 (P1_7)
UART_RST: J2.1, R86.2, TP2.1, U14.9 (~RST)
UFP_2_N: D19.3 (CH2), J7.A7 (D-), J7.B7 (D-), U13.95 (USB2UP_DM)
UFP_2_P: D19.1 (CH1), J7.A6 (D+), J7.B6 (D+), U13.94 (USB2UP_DP)
UFP_3_RXA_N: D19.5 (CH4), J7.A10 (RX2-), U13.100 (USB3UP_RXDMA)
UFP_3_RXA_P: D19.4 (CH3), J7.A11 (RX2+), U13.99 (USB3UP_RXDPA)
UFP_3_RXB_N: D20.4 (CH3), J7.B10 (RX1-), U13.85 (USB3UP_RXDMB)
UFP_3_RXB_P: D20.5 (CH4), J7.B11 (RX1+), U13.84 (USB3UP_RXDPB)
UFP_3_TXA_N: C91.2, D19.6 (CH5), U13.97 (USB3UP_TXDMA)
UFP_3_TXA_P: C92.1, D19.7 (CH6), U13.96 (USB3UP_TXDPA)
UFP_3_TXB_N: C93.2, D20.1 (CH1), U13.82 (USB3UP_TXDMB)
UFP_3_TXB_P: C94.1, D20.3 (CH2), U13.81 (USB3UP_TXDPB)
UFP_CC1: D20.6 (CH5), J7.A5 (CC1), U15.4 (CC2)
UFP_CC2: D20.7 (CH6), J7.B5 (CC2), U15.5 (CC1)
UFP_CC_CTRL: JP10.2 (C), U15.10 (CC_CRTL1)
UFP_CC_ORIENT: U13.60 (AB0/ATTCHMUX0B/GPIO3), U15.9 (CC_ORIENT)
UFP_C_ATTACH_0: U9.11 (P0_7), U13.76 (C_ATTACH0/ATTACHMUX0A/GPIO64)
UFP_DBGACC: U9.16 (P1_3), U15.6 (DBGACC_FOUND)
UFP_PD_INT: R89.1, U15.13 (INT_N)
UFP_VBUS: J7.A4 (VBUS), J7.A9 (VBUS), J7.B4 (VBUS), J7.B9 (VBUS), Q18.1 (D), Q18.2 (D), Q18.5 (D), Q18.6 (D), Q18.7 (D), Q19.1 (D), Q19.2 (D), Q19.5 (D), Q19.6 (D), Q19.7 (D), U15.2 (VBUS)
UNIT_BTN: R102.2, SW2.1, U9.19 (P1_6)
USB-A BUCK CLOCK IN: C12.1, C12.2, R12.1, U4.5 (RT/SYNC)
USB-C_BUCK_CLK_IN: R21.1, U7.33 (DEMB)

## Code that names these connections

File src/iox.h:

//{usbc car module}
//{defines.cpp}
//Copyright (C) {2023}  {mickmake}
//
//This program is free software: you can redistribute it and/or modify
//it under the terms of the GNU General Public License as published by
//the Free Software Foundation, either version 3 of the License.
//
//This program is distributed in the hope that it will be useful,
//but WITHOUT ANY WARRANTY; without even the implied warranty of
//MERCHANTABILITY or FITNESS FOR A PARTICULAR PURPOSE.  See the
//GNU General Public License for more details.
//
//You should have received a copy of the GNU General Public License
//along with this program.  If not, see <http://www.gnu.org/licenses/>.
//usbc car module
//15/09/2023
//Tokyo Andreana

#ifndef iox_h
#define iox_h

#include <Arduino.h>

//iox defines
const uint8_t iox_0_add = 0x20; //???? notshire about the addresess not shure they make sence
const uint8_t iox_1_add = 0x21;
const uint8_t iox_input_port_0 = 0x00;
const uint8_t iox_input_port_1 = 0x01;
const uint8_t iox_output_port_0 = 0x02;
const uint8_t iox_output_port_1 = 0x03;
const uint8_t iox_pol_inv_port_0 = 0x04;
const uint8_t iox_pol_inv_port_1 = 0x05;
const uint8_t iox_config_port_0 = 0x06;
const uint8_t iox_config_port_1 = 0x07;
const uint8_t iox_drive_strength_register_00 = 0x40;
const uint8_t iox_drive_strenght_register_01 = 0x41;
const uint8_t iox_drive_strenght_register_10 = 0x42;
const uint8_t iox_drive_strenght_register_11 = 0x43;
const uint8_t iox_in_latch_register_0 = 0x44;
const uint8_t iox_in_ltach_register_1 =0x45;
const uint8_t iox_pull_up_down_en_register_0 = 0x46;
const uint8_t iox_pull_up_down_en_register_1 = 0x47;
const uint8_t iox_pull_up_down_sel_register_0 = 0x48;
const uint8_t iox_pull_up_down_sel_register_1 = 0x49;
const uint8_t iox_int_mask_register_0 = 0x4a;
const uint8_t iox_int_mask_register_1 = 0x4b;
const uint8_t iox_int_stat_register_0 = 0x4c;
const uint8_t iox_int_stat_register_1 = 0x4d;
const uint8_t iox_out_port_config_register = 0x4f;

//io_call struct setup
enum in_out {
  in,       //input
  out,      //output
  bi_dir,   //bi-directional pin only used for i2c comms
  intr      //used for software interupts only works with onboard pins
};

struct pin {
  uint8_t mask;          //mask for iox
  int port;              //port on iox (can be 0 or 1 only)
  int iox_number;        //iox number
  int pin_number;        //pin number, for ESP-12F: GPIO#, for iox: phisical pin#
  in_out pin_mode;       //defines pinmode see enum above for deatails
  bool onboard;          //If true, IO is on ESP8266; if false, IO is on IO expander
  bool allow_interrupt;  //allow a given input pin to assert an interrupt only relivent for offboard pins 
  
};

//BE SHURE TO ADD PINS TO BOTH THE "pin" STRUCT AND THE "pin_names" ARRAY THEY MUST MATCH
//io_call struct defines  {mask, port, iox#, pin, pin_mode, onboard, allow_interrupt}
static struct pin sda {0x00, 0, 0, 4, bi_dir, true, false};
static struct pin scl {0x00, 0, 0, 5, bi_dir, true, false};
static struct pin onboard_led {0x00, 0, 0, 2, out, true, false};
static struct pin can_rx {0x00, 0, 0, 12, in, true, false};
static struct pin can_tx {0x00, 0, 0, 13, out, true, false};
static struct pin can_silent {0x02, 0, 0, 5, out, false, false};
static struct pin iox_0_int {0x00, 0, 1, 14, intr, true, true};
static struct pin iox_1_int {0x01, 0, 0, 4, in, false, true};
static struct pin dfp_cc_orient {0x40, 1, 1, 19, out, false, false};
static struct pin b_usbc_pgood {0x20, 0, 1, 9, in, false, true};
static struct pin b_usbc_buck_en {0x01, 1, 1, 13, out, false, false};
static struct pin b_usbc_5V_sel {0x02, 1, 1, 14, out, false, false};
static struct pin b_usbc_9V_sel {0x04, 1, 1, 15, out, false, false};
static struct pin b_usbc_12V_sel {0x08, 1, 1, 16, out, false, false};
static struct pin b_usbc_15V_sel {0x10, 1, 1, 17, out, false, false};
static struct pin b_usbc_20V_sel {0x20, 1, 1, 18, out, false, false};
static struct pin f_usbc_pgood {0x40, 0, 1, 10, in, false, true};
static struct pin f_usbc_buck_en {0x80, 0, 1, 11, out, false, false};
static struct pin f_usbc_5V_sel {0x01, 0, 1, 4, out, false, false};
static struct pin f_usbc_9V_sel {0x02, 0, 1, 5, out, false, false};
static struct pin f_usbc_12V_sel {0x04, 0, 1, 6, out, false, false};
static struct pin f_usbc_15V_sel {0x08, 0, 1, 7, out, false, false};
static struct pin f_usbc_20V_sel {0x10, 0, 1, 8, out, false, false};
static struct pin adc_alert {0x80, 1, 1, 20, in, false, true};
static struct pin ufp_c_attach_0 {0x80, 0, 0, 11, out, false, false};
static struct pin hub_vbus_det {0x40, 0, 0, 10, out, false, false};
static struct pin dfp_c_attach_1 {0x20, 0, 0, 9, out, false, false};
static struct pin disp_irq {0x10, 1, 0, 17, in, false, true};
static struct pin unit_btn {0x40, 1, 0, 19, in, false, true};
static struct pin src_btn {0x80, 1, 0, 20, in, false, true};
static struct pin mode_btn {0x20, 0, 0, 18, in, false, true};
static struct pin iox_0_p_0_0 {0X08, 0, 0, 7, in, false, false};
static struct pin iox_0_p_0_1 {0X04, 0, 0, 6, in, false, false};
static struct pin ufp_dbgacc {0x08, 1, 0, 16, in, false, false};
static struct pin dfp_dbgacc {0x04, 1, 0, 15, in, false, false};
static struct pin ufp_alert_n {0x02, 1, 0, 14, in, false, true};
static struct pin dfp_alert_n {0x01, 1, 0, 13, in, false, true};
static struct pin ufp_cc_orient {0x10, 0, 0, 8, out, false, false};


//io_call pin struct names for auto pin init
static struct pin* pin_names[] = {
  &sda,
  &scl,
  &onboard_led,
  &can_rx,
  &can_tx,
  &can_silent,
  &iox_0_int,
  &iox_1_int,
  &pgood_21V,
  &b_usbc_pgood,
  &b_usbc_buck_en,
  &b_usbc_5V_sel,
  &b_usbc_9V_sel,
  &b_usbc_12V_sel,
  &b_usbc_15V_sel,
  &b_usbc_20V_sel,
  &f_usbc_pgood,
  &f_usbc_buck_en,
  &f_usbc_5V_sel,
  &f_usbc_9V_sel,
  &f_usbc_12V_sel,
  &f_usbc_15V_sel,
  &f_usbc_20V_sel,
  &adc_alert,
  &ufp_c_attach_0,
  &hub_vbus_det,
  &dfp_c_attach_1,
  &disp_irq,
  &unit_btn,
  &src_btn,
  &mode_btn,
  &iox_0_p_0_0,
  &iox_0_p_0_1,
  &ufp_dbgacc,
  &dfp_dbgacc,
  &tp16,
  &tp17,
  &tp18

} ;


//read write enum define for io_call function
enum read_write {
  read,
  write
};

//io_call high low input enum
enum high_low {
  high,
  low,
  read_mode
};

//fuction defines
uint8_t read_current_io_state(int port, int iox_num);
int io_call(struct pin pin_needed, enum read_write read_write, enum high_low high_low);
void gpio_init();



#endif // iox_h

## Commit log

2023-09-09 inital commit
2023-09-09 working on adujustabel otpur for usbpd
2023-09-09 making hardware progress
2023-09-10 working on usb side implimentaion
2023-09-10 fixed desync
2023-09-15 working on io fugtions
2023-09-15 working on io_call and auto init for pins
2023-09-21 working on biuld info setup
2023-09-21 addiing bild info
2023-09-21 messing with firmware biuld info
2023-09-22 gave up on ebedding date and time in the firmware workingon adding the adc
2023-09-22 still working on adc
2023-09-23 working on hardware agin as well as implimentded auto adc init and read
2023-09-26 finnished rudimentry schimatics still needs alot of work
2023-09-26 working on display implimentation
2023-09-26 modifyed gitignore to ignore user lock files
2023-09-27 working on hardware
2023-09-28 working assighning footprints still
2023-09-29 FINALY starting the pcb
2023-09-29 coldent sleep so came back and did somre routing
2023-09-30 working on routing still finnished psu section
2023-10-01 worked on usb port and display routing
2023-10-02 working in final routing
2023-10-09 finaliseing pcb layout will come back later for a fresh look
2023-10-09 fixed an oopsy
2023-10-18 messing arround with pcb to finalise
2023-10-18 fixed platformio.ini
2023-10-20 fialiseing pcb for production
2023-11-20 ned to fix port swap before prod
2023-11-24 working on fixing pcb impeedance
2023-11-24 fixing some spelling
2023-11-25 moving defines to a sepreate file to improve readability
2024-01-10 doing stuff
2024-02-18 fixed DP issues and finneshed overall routeing
2024-02-18 minor revisons
2024-02-19 minor revisions
2024-02-26 minor pre prod chnages
2024-02-27 Delete hardware/REV_A.pdf
    outdated
2024-02-27 working on firmware more
2024-02-27 more firmware work
2024-02-28 more firmware work and refactoring
2024-02-28 working on display functions
2024-02-28 begain work on usbpd implimentation
2024-02-29 working on usb pd implimentation
2024-02-29 working on complie issues
2024-03-01 fixed linking
2024-03-01 added programming guide for ptn5110n
2024-03-01 woring on firmware
2024-03-01 switched pd phy as old one needed an NDA
2024-03-04 working on usb pd protocol implimentation
2024-03-04 just a bit more work
2024-03-05 fixingt things
2024-03-05 stilworking on firmware
2024-03-05 working firmware stil
2024-03-06 working on things
2024-03-06 minor pcb change
2024-03-06 fixed_watchdog hang from pd_phy_init
2024-03-06 working on some stuff
2024-03-06 working on intrupt handeling
2024-03-08 worked or intrupt handeler some more
2024-03-08 started work on ui
2024-03-12 working on the pd protpcol implimentation
2024-03-13 fiexed a few small things
2024-03-13 trying to get gmp to work
2024-03-13 working on pd protocall
2024-03-14 timer
2024-03-17 starting to attempt to impliment pd policy engine
2024-03-17 working on pd policy engine
2024-03-18 stuff
2024-04-09 updated schimatic pdf
2024-04-29 migrated to kicad 8
2024-04-30 updated block digram minor pcb changes
2024-05-22 improved documentation fixed timer controler and fixed wifi
2024-05-22 added eeprom for nonvol memory
2024-05-26 fixed a shiton of spelling mistakes and some minor refactoring
2024-05-26 fixed some copilot fuckups
2024-05-30 trying to get wifi setup over serial
2024-05-31 working on wifi
2024-05-31 ignore wifi credentals
2024-07-31 switched can tranceiver to combo controler and tranceiver
2024-07-31 minor work and coppying blocks for other projects
2024-09-22 added some debugging fuctionality
2024-11-13 fixed debugging system
2024-11-14 workiing on some inturpt otimiseation and pin init issues
2024-11-16 kicad version upgrade and minor pcb changes
2024-11-16 working on io changes still
2024-11-19 finnished with itrupt handleing for now
2025-08-01 migrated to the esp32-s2 and starting new board revison
